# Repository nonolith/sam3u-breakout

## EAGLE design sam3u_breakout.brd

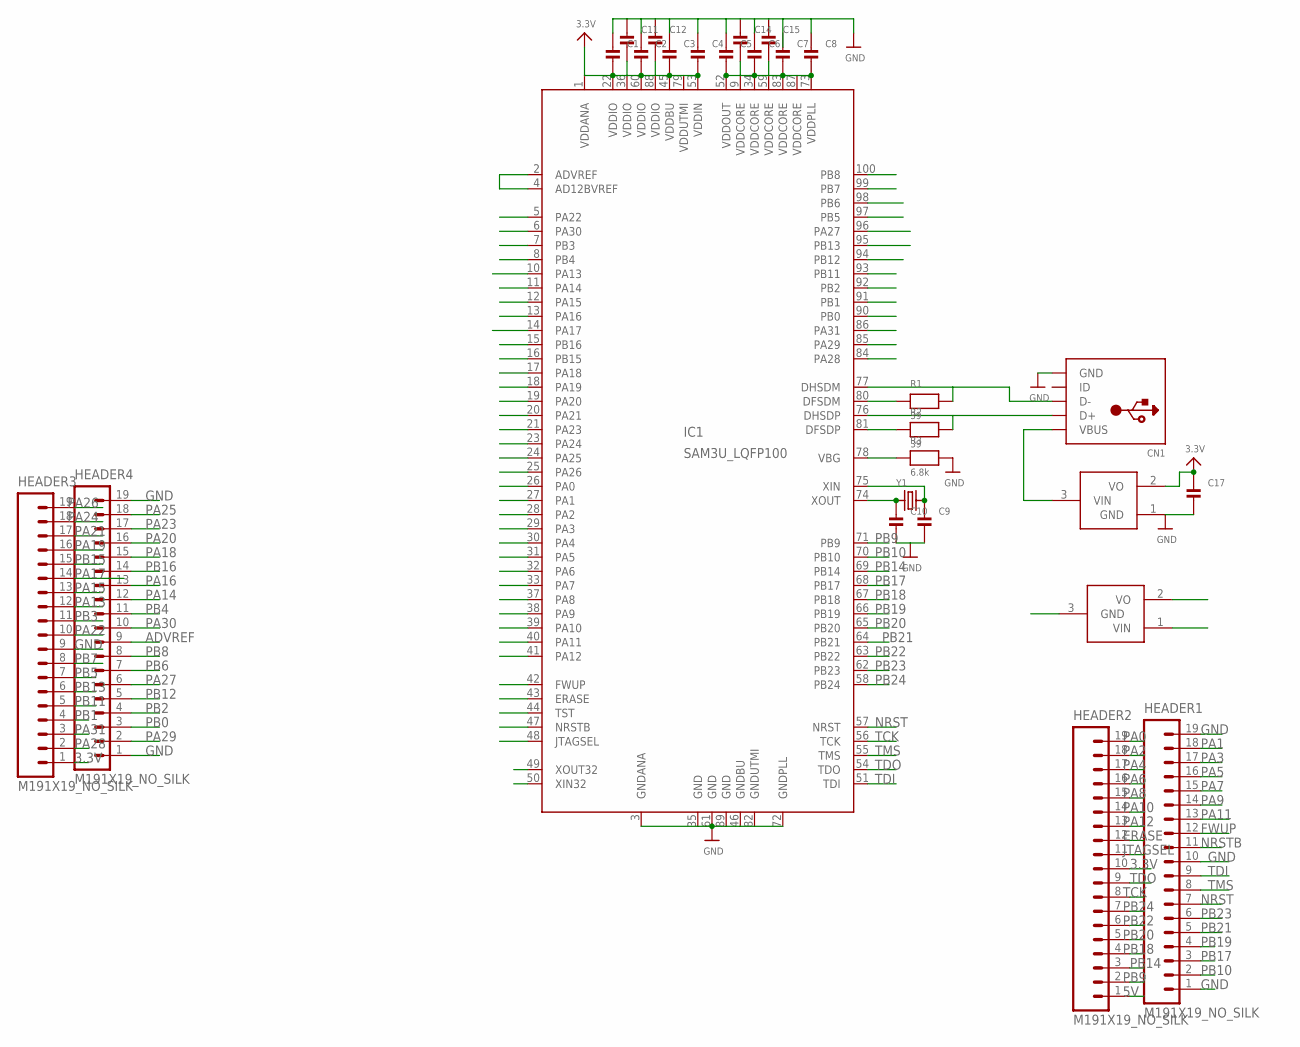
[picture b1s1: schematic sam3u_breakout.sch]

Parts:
C1, C2, C3, C4, C5, C6, C7, C8, C9, C10, C11, C12, C14, C15, C17: CAP_CERAMIC0402; 0402
CN1: USBMICROB; USB-MICROB
HEADER1, HEADER2, HEADER3, HEADER4: M191X19_NO_SILK; 1X19_NO_SILK
IC1: SAM3U_LQFP100; LQFP100
R1, R2: 39; 0603
R3: 6.8k; 0603
U$7: VREG; SOT23-3
U$14: VREF; SOT23-3
Y1: CRYSTALSMD; HC49UP

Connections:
1.8V: C5.2, C6.2, C7.2, C8.2, C14.2, C15.2, IC1.9 (VDDCORE), IC1.34 (VDDCORE), IC1.52 (VDDOUT), IC1.59 (VDDCORE), IC1.73 (VDDPLL), IC1.83 (VDDCORE), IC1.87 (VDDCORE)
3.3V: C1.2, C2.2, C3.2, C4.2, C11.2, C12.2, C17.1, HEADER2.10, HEADER3.1, IC1.1 (VDDANA), IC1.22 (VDDIO), IC1.36 (VDDIO), IC1.45 (VDDBU), IC1.53 (VDDIN), IC1.60 (VDDIO), IC1.79 (VDDUTMI), IC1.88 (VDDIO), U$7.2 (VO), U$14.1 (VIN)
5V: CN1.P1 (VBUS), HEADER2.1, U$7.3 (VIN)
ADVREF: HEADER4.9, IC1.2 (ADVREF), IC1.4 (AD12BVREF), U$14.2 (VO)
ERASE: HEADER2.12, IC1.43 (ERASE)
FWUP: HEADER1.12, IC1.42 (FWUP)
GND: C1.1, C2.1, C3.1, C4.1, C5.1, C6.1, C8.1, C9.2, C10.2, C11.1, C12.1, C14.1, C15.1, C17.2, CN1.P5 (GND), HEADER1.1, HEADER1.10, HEADER1.19, HEADER3.9, HEADER4.1, HEADER4.19, IC1.3 (GNDANA), IC1.35 (GND), IC1.46 (GNDBU), IC1.61 (GND), IC1.72 (GNDPLL), IC1.82 (GNDUTMI), IC1.89 (GND), R3.2, U$7.1 (GND), U$14.3 (GND)
JTAGSEL: HEADER2.11, IC1.48 (JTAGSEL)
unnamed: CN1.P3 (D+), IC1.76 (DHSDP), R2.2
unnamed: IC1.80 (DFSDM), R1.1
unnamed: IC1.81 (DFSDP), R2.1
unnamed: CN1.P2 (D-), IC1.77 (DHSDM), R1.2
unnamed: IC1.78 (VBG), R3.1
unnamed: C9.1, IC1.75 (XIN), Y1.2
unnamed: C10.1, IC1.74 (XOUT), Y1.1
NRST: HEADER1.7, IC1.57 (NRST)
NRSTB: HEADER1.11, IC1.47 (NRSTB)
PA0: HEADER2.19, IC1.26 (PA0)
PA1: HEADER1.18, IC1.27 (PA1)
PA2: HEADER2.18, IC1.28 (PA2)
PA3: HEADER1.17, IC1.29 (PA3)
PA4: HEADER2.17, IC1.30 (PA4)
PA5: HEADER1.16, IC1.31 (PA5)
PA6: HEADER2.16, IC1.32 (PA6)
PA7: HEADER1.15, IC1.33 (PA7)
PA8: HEADER2.15, IC1.37 (PA8)
PA9: HEADER1.14, IC1.38 (PA9)
PA10: HEADER2.14, IC1.39 (PA10)
PA11: HEADER1.13, IC1.40 (PA11)
PA12: HEADER2.13, IC1.41 (PA12)
PA13: HEADER3.12, IC1.10 (PA13)
PA14: HEADER4.12, IC1.11 (PA14)
PA15: HEADER3.13, IC1.12 (PA15)
PA16: HEADER4.13, IC1.13 (PA16)
PA17: HEADER3.14, IC1.14 (PA17)
PA18: HEADER4.15, IC1.17 (PA18)
PA19: HEADER3.16, IC1.18 (PA19)
PA20: HEADER4.16, IC1.19 (PA20)
PA21: HEADER3.17, IC1.20 (PA21)
PA22: HEADER3.10, IC1.5 (PA22)
PA23: HEADER4.17, IC1.21 (PA23)
PA24: HEADER3.18, IC1.23 (PA24)
PA25: HEADER4.18, IC1.24 (PA25)
PA26: HEADER3.19, IC1.25 (PA26)
PA27: HEADER4.6, IC1.96 (PA27)
PA28: HEADER3.2, IC1.84 (PA28)
PA29: HEADER4.2, IC1.85 (PA29)
PA30: HEADER4.10, IC1.6 (PA30)
PA31: HEADER3.3, IC1.86 (PA31)
PB0: HEADER4.3, IC1.90 (PB0)
PB1: HEADER3.4, IC1.91 (PB1)
PB2: HEADER4.4, IC1.92 (PB2)
PB3: HEADER3.11, IC1.7 (PB3)
PB4: HEADER4.11, IC1.8 (PB4)
PB5: HEADER3.7, IC1.97 (PB5)
PB6: HEADER4.7, IC1.98 (PB6)
PB7: HEADER3.8, IC1.99 (PB7)
PB8: HEADER4.8, IC1.100 (PB8)
PB9: HEADER2.2, IC1.71 (PB9)
PB10: HEADER1.2, IC1.70 (PB10)
PB11: HEADER3.5, IC1.93 (PB11)
PB12: HEADER4.5, IC1.94 (PB12)
PB13: HEADER3.6, IC1.95 (PB13)
PB14: HEADER2.3, IC1.69 (PB14)
PB15: HEADER3.15, IC1.16 (PB15)
PB16: HEADER4.14, IC1.15 (PB16)
PB17: HEADER1.3, IC1.68 (PB17)
PB18: HEADER2.4, IC1.67 (PB18)
PB19: HEADER1.4, IC1.66 (PB19)
PB20: HEADER2.5, IC1.65 (PB20)
PB21: HEADER1.5, IC1.64 (PB21)
PB22: HEADER2.6, IC1.63 (PB22)
PB23: HEADER1.6, IC1.62 (PB23)
PB24: HEADER2.7, IC1.58 (PB24)
TCK: HEADER2.8, IC1.56 (TCK)
TDI: HEADER1.9, IC1.51 (TDI)
TDO: HEADER2.9, IC1.54 (TDO)
TMS: HEADER1.8, IC1.55 (TMS)
TST: IC1.44 (TST)

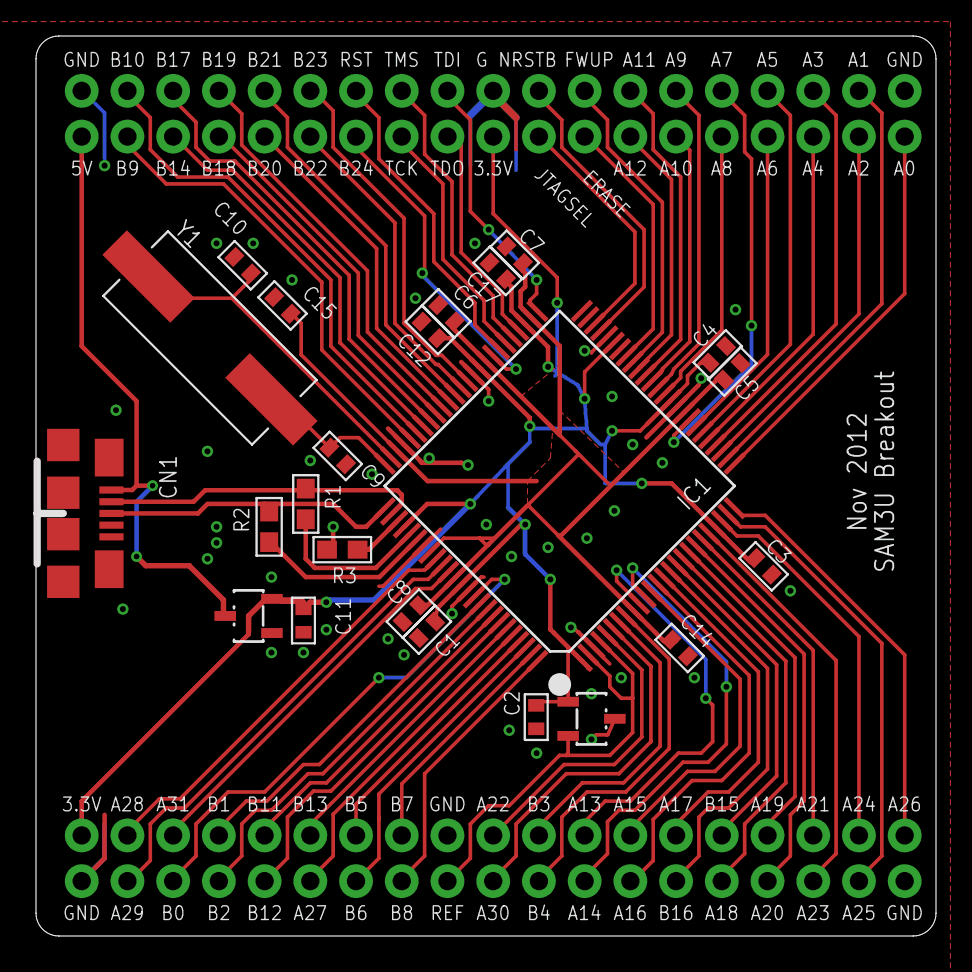
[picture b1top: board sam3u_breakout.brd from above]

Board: 2 copper layers, 50.0 x 50.0 mm, 27 parts (0 on the bottom side), 78 nets.

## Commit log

2012-05-25 Power and USB
2012-11-07 Manually hack the .sch with a text editor to make it open (failed library change)
2012-11-07 Route board
2012-11-08 Labels
2012-11-08 s/miniusb/microusb/

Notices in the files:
parts and their libraries:
SparkFun-Connectors: Licensing: CC v3.0 Share-Alike You are welcome to use this library for commercial purposes.
